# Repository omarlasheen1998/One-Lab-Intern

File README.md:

# One-Lab-Intern
codes and  pcb designed during sensor interfacing intern at one Lab

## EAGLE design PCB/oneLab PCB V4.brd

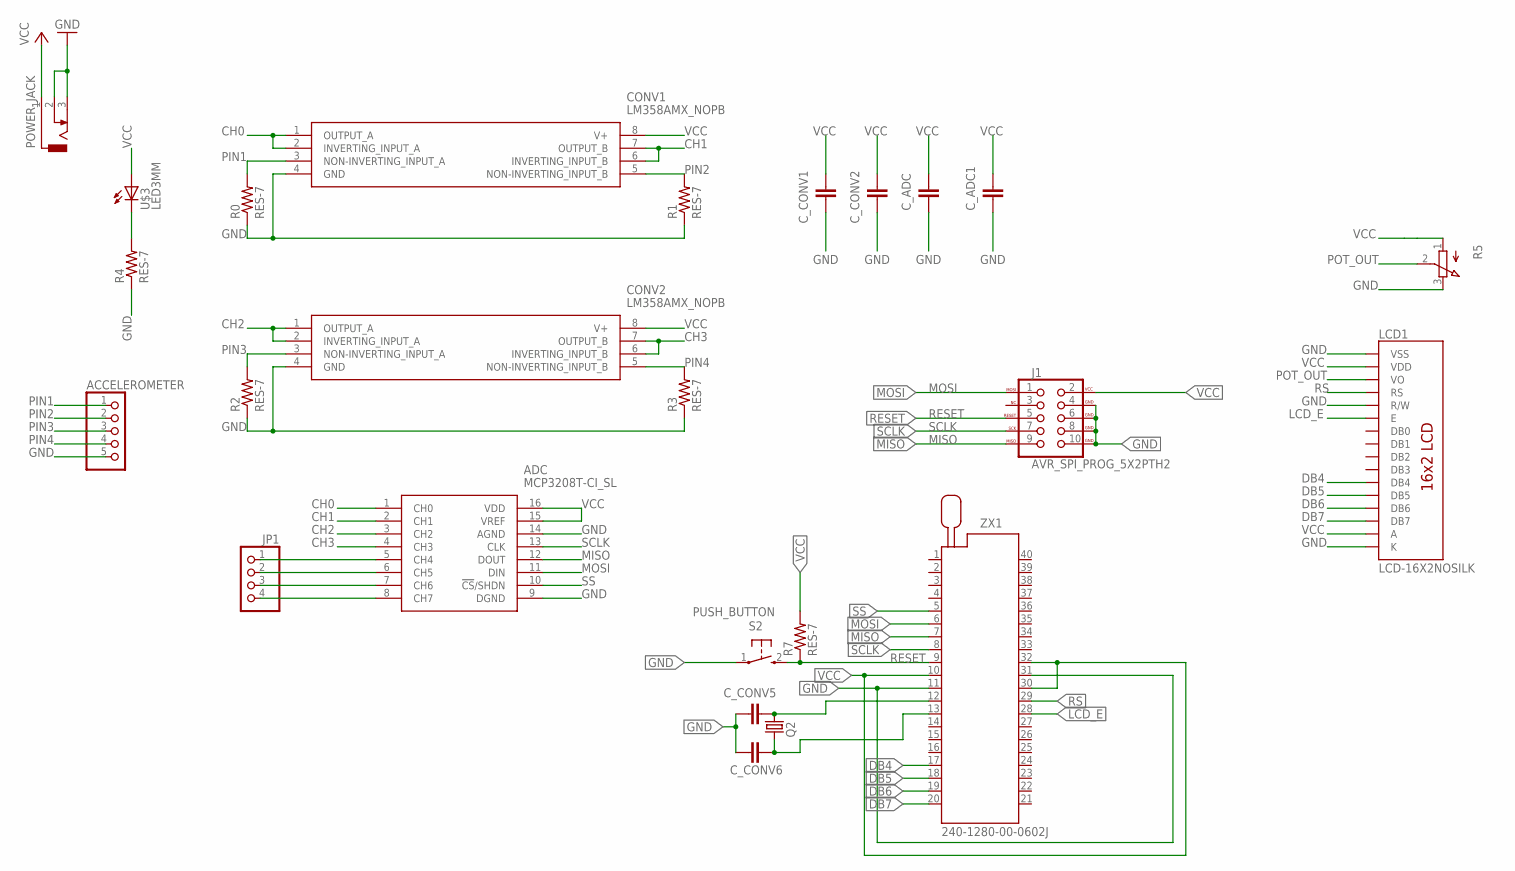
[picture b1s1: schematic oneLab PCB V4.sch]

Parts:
ACCELEROMETER: PINHD-5_DATA; 1X05_DATA
ADC: MCP3208T-CI_SL; SOIC127P600X175-16N
CONV1, CONV2: LM358AMX_NOPB; SOIC127P600X175-8N
C_ADC, C_ADC1: CAPACITOR; C025-025X050
C_CONV1, C_CONV2, C_CONV5, C_CONV6: CAPACITOR; C025-025X050
J1: AVR_SPI_PROG_5X2PTH2; 2X5-SHROUDED
JP1: PINHD-4_DATA; 1X04_DATA
LCD1: LCD-16X2NOSILK; LCD-16X2_NOSILK
POWER_JACK: CON_JACK; DCJ0303
Q2: CRYSTALHC49U-V; HC49U-V
R0, R1, R2, R3, R4, R7: RES-7; 0204/7
R5: POT; 3RP/1610N
S2: PUSH_BUTTON; B3F-10XX
U$3: LED3MM
ZX1: 240-1280-00-0602J

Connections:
CH0: ADC.1 (CH0), CONV1.1 (OUTPUT_A), CONV1.2 (INVERTING_INPUT_A)
CH1: ADC.2 (CH1), CONV1.6 (INVERTING_INPUT_B), CONV1.7 (OUTPUT_B)
CH2: ADC.3 (CH2), CONV2.1 (OUTPUT_A), CONV2.2 (INVERTING_INPUT_A)
CH3: ADC.4 (CH3), CONV2.6 (INVERTING_INPUT_B), CONV2.7 (OUTPUT_B)
DB4: LCD1.11 (DB4), ZX1.17
DB5: LCD1.12 (DB5), ZX1.18
DB6: LCD1.13 (DB6), ZX1.19
DB7: LCD1.14 (DB7), ZX1.20
GND: ACCELEROMETER.5, ADC.9 (DGND), ADC.14 (AGND), CONV1.4 (GND), CONV2.4 (GND), C_ADC.2, C_ADC1.2, C_CONV1.2, C_CONV2.2, C_CONV5.1, C_CONV6.1, J1.4 (GND), J1.6 (GND), J1.8 (GND), J1.10 (GND), LCD1.1 (VSS), LCD1.5 (R/W), LCD1.16 (K), POWER_JACK.2, POWER_JACK.3, R0.1, R1.1, R2.1, R3.1, R4.1, R5.3 (E), S2.1, ZX1.11, ZX1.31
LCD_E: LCD1.6 (E), ZX1.28
MISO: ADC.12 (DOUT), J1.9 (MISO), ZX1.7
MOSI: ADC.11 (DIN), J1.1 (MOSI), ZX1.6
unnamed: ADC.5 (CH4), JP1.1
unnamed: ADC.6 (CH5), JP1.2
unnamed: ADC.7 (CH6), JP1.3
unnamed: ADC.8 (CH7), JP1.4
unnamed: C_CONV5.2, Q2.2, ZX1.12
unnamed: R4.2, U$3.K (C)
unnamed: C_CONV6.2, Q2.1, ZX1.13
PIN1: ACCELEROMETER.1, CONV1.3 (NON-INVERTING_INPUT_A), R0.2
PIN2: ACCELEROMETER.2, CONV1.5 (NON-INVERTING_INPUT_B), R1.2
PIN3: ACCELEROMETER.3, CONV2.3 (NON-INVERTING_INPUT_A), R2.2
PIN4: ACCELEROMETER.4, CONV2.5 (NON-INVERTING_INPUT_B), R3.2
POT_OUT: LCD1.3 (VO), R5.2 (S)
RESET: J1.5 (RESET), R7.1, S2.2 (S), ZX1.9
RS: LCD1.4 (RS), ZX1.29
SCLK: ADC.13 (CLK), J1.7 (SCK), ZX1.8
SS: ADC.10 (!CS!/SHDN), ZX1.5
VCC: ADC.15 (VREF), ADC.16 (VDD), CONV1.8 (V+), CONV2.8 (V+), C_ADC.1, C_ADC1.1, C_CONV1.1, C_CONV2.1, J1.2 (VCC), LCD1.2 (VDD), LCD1.15 (A), POWER_JACK.1, R5.1 (A), R7.2, U$3.A, ZX1.10, ZX1.30, ZX1.32

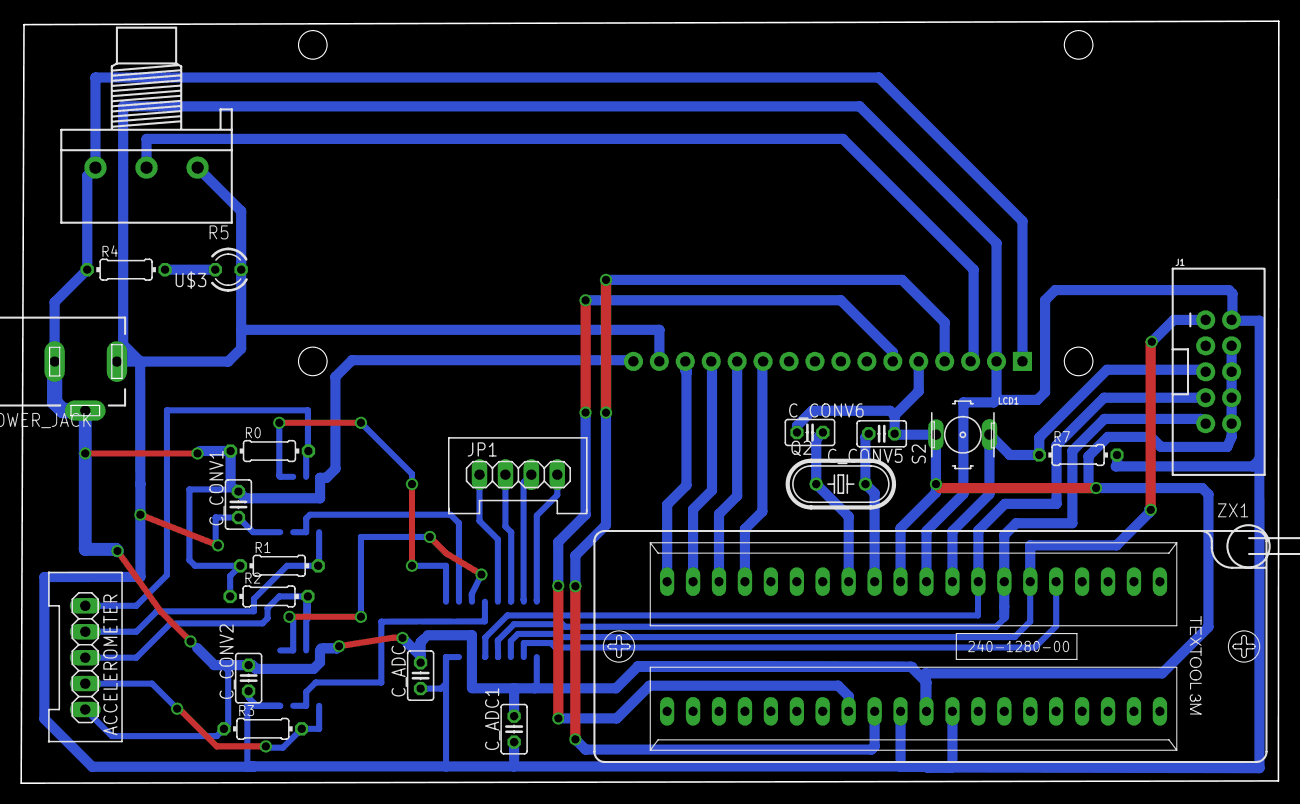
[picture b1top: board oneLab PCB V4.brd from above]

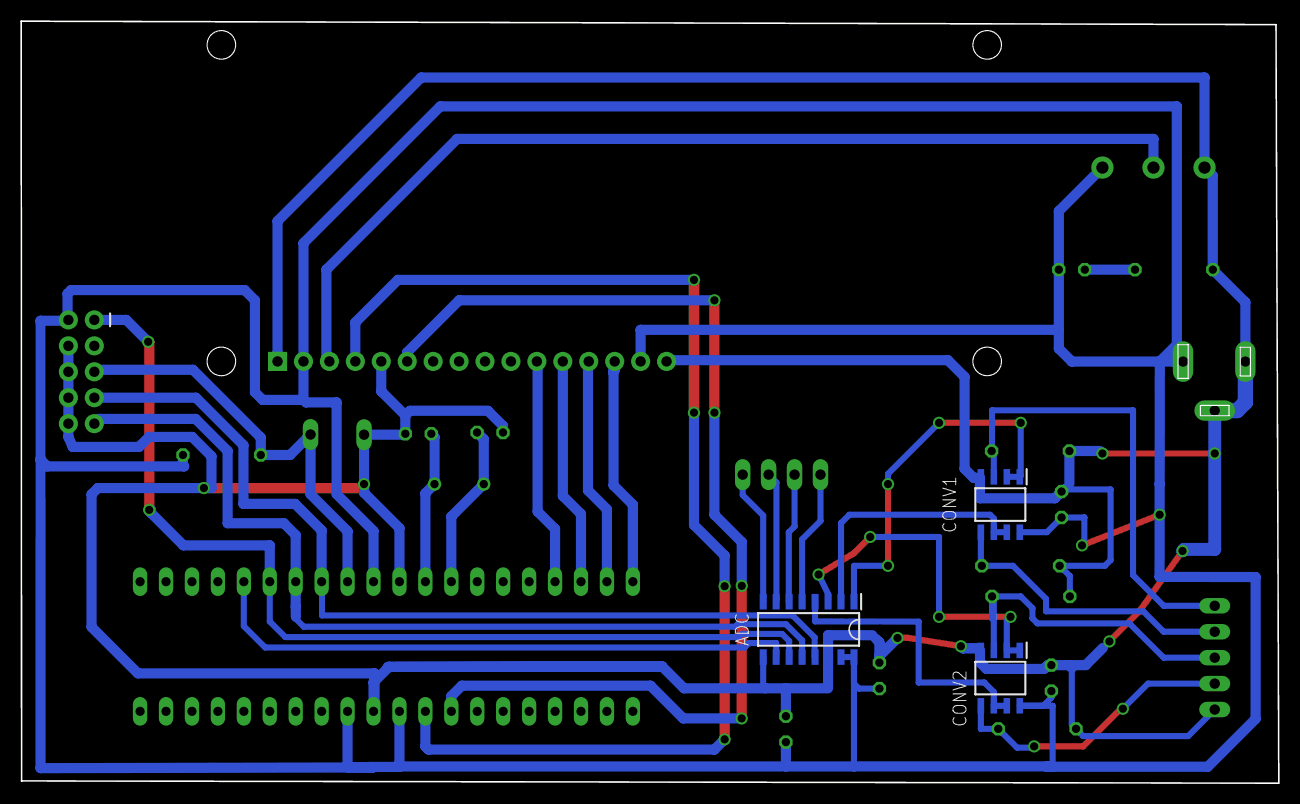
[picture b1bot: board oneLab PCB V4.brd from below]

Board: 2 copper layers, 123.2 x 74.6 mm, 25 parts (3 on the bottom side), 29 nets.
